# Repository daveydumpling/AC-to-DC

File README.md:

Attached is the zip file containing my PCB design for converting AC to DC. It has been designed fully on KiCad 8.0. 
This is my first PCB design. I have designed it to fit a 150 X 100 mm copper clad for etching. 

Also, 3 PNG files of the layout have been attached too, for a good three dimensional view of my design.

The purpose of this design is to convert 12 V AC to 5V DC as well as 12V DC. 

Kindly Note: The stepdown transformer to convert 230V AC to 12 V AC hasn't been included in the schematic; But there is sufficient space available on the board to accommodate for it's installation.

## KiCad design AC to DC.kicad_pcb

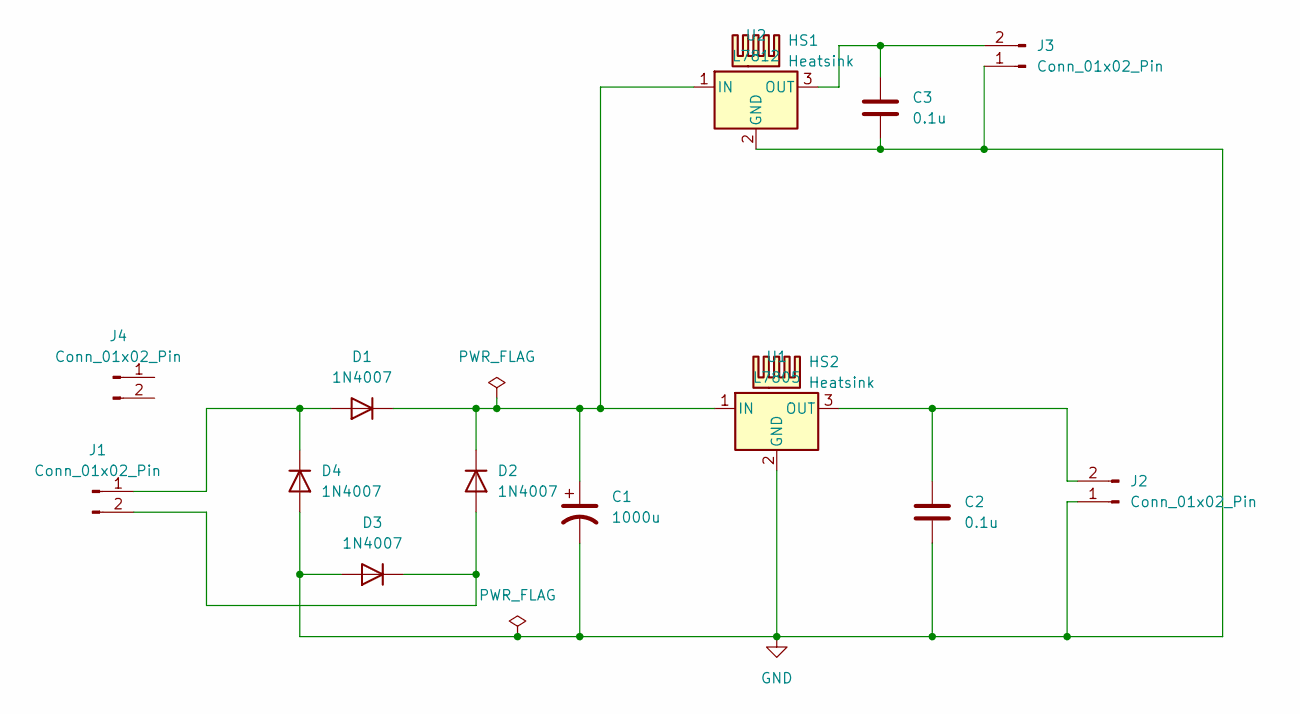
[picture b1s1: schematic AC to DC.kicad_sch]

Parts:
C1: 1000u; CP_Radial_D5.0mm_P2.50mm
C2, C3: 0.1u; C_Disc_D3.4mm_W2.1mm_P2.50mm
D1, D2, D3, D4: 1N4007; D_DO-41_SOD81_P10.16mm_Horizontal
HS1, HS2: Heatsink; Heatsink_Stonecold_HS-S03_13.21x12.7mm
J1, J2, J3, J4: Conn_01x02_Pin; TerminalBlock_Phoenix_MKDS-1,5-2_1x02_P5.00mm_Horizontal
U1: L7805; TO-220-3_Vertical
U2: L7812; TO-220-3_Vertical

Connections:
GND: C1.2, C2.2, C3.2, D3.2 (A), D4.2 (A), J2.1, J3.1, U1.2 (GND), U2.2 (GND)
unnamed: D1.2 (A), D4.1 (K), J1.1
unnamed: C1.1, D1.1 (K), D2.1 (K), U1.1 (IN), U2.1 (IN)
unnamed: D2.2 (A), D3.1 (K), J1.2
unnamed: C2.1, J2.2, U1.3 (OUT)
unnamed: C3.1, J3.2, U2.3 (OUT)

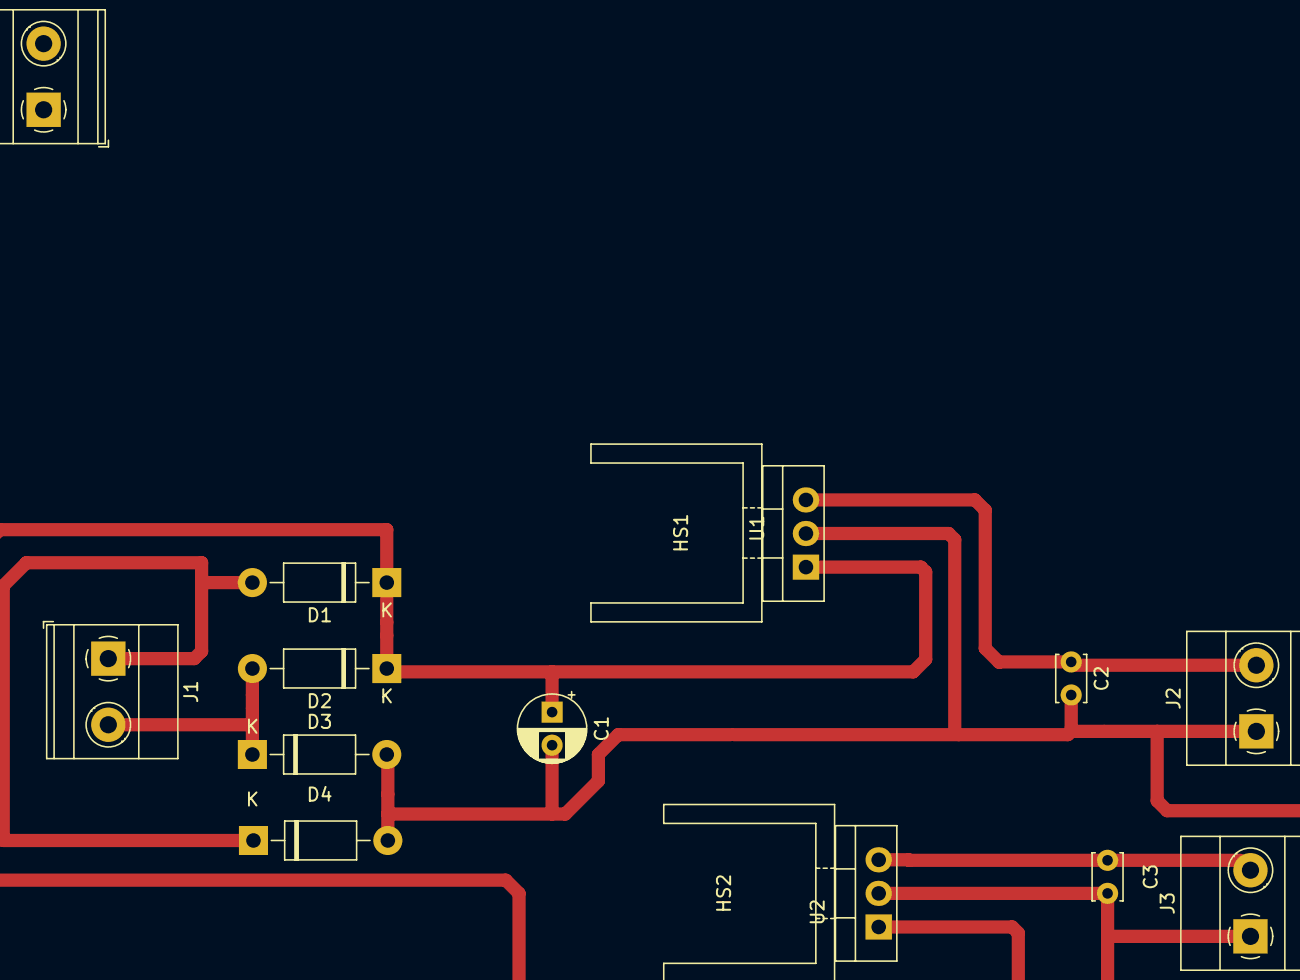
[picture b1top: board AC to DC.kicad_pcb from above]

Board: 2 copper layers, 15 parts (0 on the bottom side), 6 nets.

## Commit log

2024-11-11 first commit yay!
2024-11-11 added all teh SVGs
2024-11-11 added all PNGs
2024-11-11 removed unnecessary images
2024-11-11 added readme
2024-11-11 new future
2024-11-18 Add files via upload
    Attached is the zip file containing my PCB design for converting AC to DC. It has been designed fully on KiCad 8.0.
    This is my first PCB design. I have designed it to fit a 150 X 100 mm copper clad for etching.
    The purpose of this design is to convert 12 V AC to 5V DC as well as 12V DC.
    Kindly Note: The stepdown transformer to convert 230V AC to 12 V AC hasn't been included here in this design but there is sufficient space available on the board to accommodate for it's installation.
2024-11-18 README.md
    Read if interested in utilizing for projects.
2024-11-18 README.md
